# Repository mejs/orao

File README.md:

Orao: Yugoslav 8-bit school microcomputer
=====================================

Orao was an 8-bit computer developed by Miroslav Kocijan for PEL Varaždin in 1984. This repo includes roms, programs and tools for working with this computer. 

I've built a replica of this computer based on [Josip Perušanec's Orao 2007 project](http://www.deltasoft.com.hr/projects/orao2007.php?title=Orao%202007). This replica is fully compatible with the original, but it uses a single EPROM and RAM instead of multiple ones like the original.

### [Roms](https://github.com/mejs/orao/tree/master/roms)
There were 2 roms for the Orao:
* ROM 102: first rom version with basic (sic) BASIC and monitor program. This rom is in BCS.
* ROM 103: second rom version with advanced BASIC and monitor program. This rom is in English

Both of these roms were originally stored on two 2764 EPROMs, one would have the BASIC and the other the monitor. The version I have here combines both the 102 and 103 ROM versions with both BASIC and monitor into a single hex bin for loading onto a 27256 EPROM.

### [Orao rs232](https://github.com/mejs/orao/tree/master/orao_rs232)

The Orao has a built in RS232 TX meant for use with a printer, but no built in RX. In order to enable two way serial communication I built a 6551 based rs232 adapter. A gerbers file and a BOM are attached. I wrote a simple terminal emulator which consists of a BASIC and 6502 assembly. I'm still testing the interface.

### [Orao keyboard](https://github.com/mejs/orao/tree/master/orao_keyboard)

Since I don't own an original Orao, I needed a way to connect a regular PS2 keyboard to the replica. This is a work in progress project for an Arduino based interface that uses an MT8816 analog switch matrix to use a PS2 keyboard with the Orao. The interface supports all Orao keys and key combinations including PF keys, control and shift key support. You can find the list of all Orao key combinations [here (in BCS)](https://github.com/mejs/orao/tree/master/orao_keyboard/combinations.png) I've used an Arduino Nanofor testing.

Orao's keyboard input works by shorting connections between 6 data lines (D4-D7) and 10 address lines (A0-A9). When a key is pressed, the connection is shorted between corresponding lines to input a key press. I.e., to type "A", the key short address line A7 and data line D5. MT8816 is an analog switch relay. It contains a 8 x 16 array of crosspoint switches along with a 7 to 128 line decoder and latch circuits. The 8 lines are labeled Y0-Y7, and the 16 lines are labelled X0-X15. MT8816 can connect any Y line with any X line, and it can make multiple concurrent connections. Y1 to Y6 lines are connected to Orao's keyboard connector pins 1-6 (data lines D4-D7), and X0 to X9 are connected to Orao keyboard connector pins 7-16 (address lines A0-A9).

MT8816 connections are selected by seting bits on address inputs AX0-Ax3 and AY0-AY3. The addresses are defined in the [MT8816 datasheet](https://github.com/mejs/orao/tree/master/orao_keyboard/MT8816-datasheet.pdf) in Table 1 - Address Decode Truth Table on page 11. Address inputs are connected to Arduino digital I/O pins 8-14. Arduino uses PS2KeyAdvanced library to read keycodes from the connected PS/2 keyboard, connected to digital I/O pins 2 and 3. When a key is pressed (i.e. 32833 for A), Arduino sets the bits on the address inputs (1100101 for A), raises MT8816 data pin to save it to memory, raises and lowers strobe, holds for 22ms, then lowers data and raises reset. This makes the connection between A7 and D5 on the Orao.

Due to the physical difference between modern, Model-M compatible keyboards and Orao's keyboard, I've made the following key placement decisions:

* Insert key is used for * : Orao key
* Home key is used for / ? Orao key
* Backspace is used as left arrow key in addition to the actual left arrow key because it effectively works as backspace

This project was inspired by Marko Šolajić's [galaksija-keyboard-interface project](https://github.com/msolajic/galaksija-keyboard-interface) and the [C64-keyboard project](https://github.com/Hartland/C64-Keyboard)

I've designed and manufactured a board that can mount into the keyboard socket on the Orao 2007 clone. The Eagle files are available [here](https://github.com/mejs/orao/tree/master/orao_keyboard/eagle) and the gerber files are [here](https://github.com/mejs/orao/tree/master/orao_keyboard/gerbers).

### [Orao 2007 Gerbers](https://github.com/mejs/orao/tree/master/schematics)

The gerbers files hosted on Josip Perušanec's website include [one connection missing in the gerbers](https://twitter.com/mejs/status/1338876219308322817), preventing video output without an additional jumper. The version hosted here fixes this.

### [Manuals](https://github.com/mejs/orao/tree/master/manuals)

I've used a number of manuals while working on the Orao, especially the manual for the never released DIY kit that was [posted online by RetroInfo](https://retroinfo.hr/dvije-knjige-za-pel-orao/).

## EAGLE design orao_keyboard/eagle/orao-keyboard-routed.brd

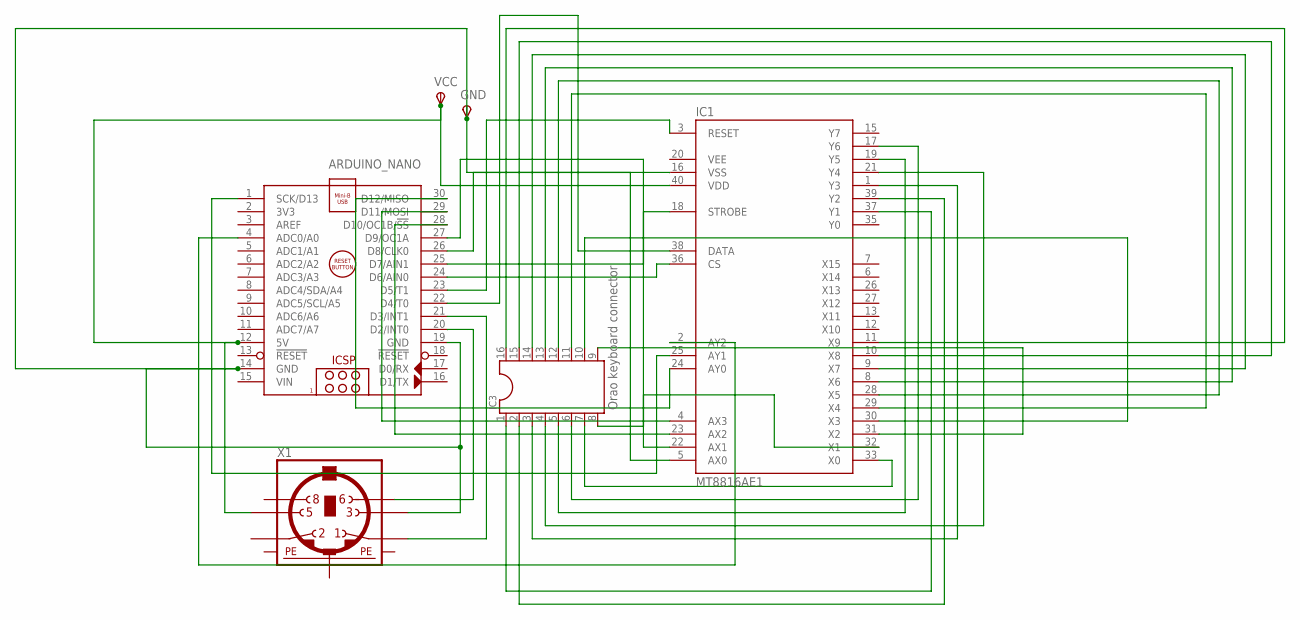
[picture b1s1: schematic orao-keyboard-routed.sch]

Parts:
ARDUINO_NANO: ARDUINO_NANO
GND: TPSPAD1-13; P1-13
IC1: MT8816AE1; DIL40
IC3: Orao keyboard connector; SOCKED-16
VCC: TPSPAD1-13; P1-13
X1: MINI_DIN_6; M_DIN6

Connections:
unnamed: ARDUINO_NANO.20 (D2/INT0), X1.6
unnamed: ARDUINO_NANO.21 (D3/INT1), X1.1
unnamed: IC1.37 (Y1), IC3.1
unnamed: IC1.39 (Y2), IC3.2
unnamed: IC1.1 (Y3), IC3.3
unnamed: IC1.21 (Y4), IC3.4
unnamed: IC1.19 (Y5), IC3.5
unnamed: IC1.17 (Y6), IC3.6
unnamed: IC1.33 (X0), IC3.7
unnamed: IC1.32 (X1), IC3.8
unnamed: IC1.31 (X2), IC3.9
unnamed: IC1.30 (X3), IC3.10
unnamed: IC1.29 (X4), IC3.11
unnamed: IC1.28 (X5), IC3.12
unnamed: IC1.8 (X6), IC3.13
unnamed: IC1.9 (X7), IC3.14
unnamed: IC1.10 (X8), IC3.15
unnamed: IC1.11 (X9), IC3.16
unnamed: ARDUINO_NANO.22 (D4/T0), IC1.38 (DATA)
unnamed: ARDUINO_NANO.23 (D5/T1), IC1.3 (RESET)
unnamed: ARDUINO_NANO.24 (D6/AIN0), IC1.36 (CS)
unnamed: ARDUINO_NANO.25 (D7/AIN1), IC1.18 (STROBE)
unnamed: ARDUINO_NANO.26 (D8/CLK0), IC1.5 (AX0)
unnamed: ARDUINO_NANO.27 (D9/OC1A), IC1.22 (AX1)
unnamed: ARDUINO_NANO.28 (D10/OC1B/!SS), IC1.23 (AX2)
unnamed: ARDUINO_NANO.29 (D11/MOSI), IC1.4 (AX3)
unnamed: ARDUINO_NANO.30 (D12/MISO), IC1.24 (AY0)
unnamed: ARDUINO_NANO.1 (SCK/D13), IC1.25 (AY1)
unnamed: ARDUINO_NANO.4 (ADC0/A0), IC1.2 (AY2)
unnamed: ARDUINO_NANO.12 (5V), IC1.40 (VDD), VCC.TP, X1.5
unnamed: ARDUINO_NANO.14 (GND), ARDUINO_NANO.19 (GND), GND.TP, IC1.16 (VSS), X1.3
PE1: X1.SH1 (PE1)
PE2: X1.SH2 (PE2)
PE3: X1.SH3 (PE3)
VEE: IC1.20 (VEE)
VIN: ARDUINO_NANO.15 (VIN)

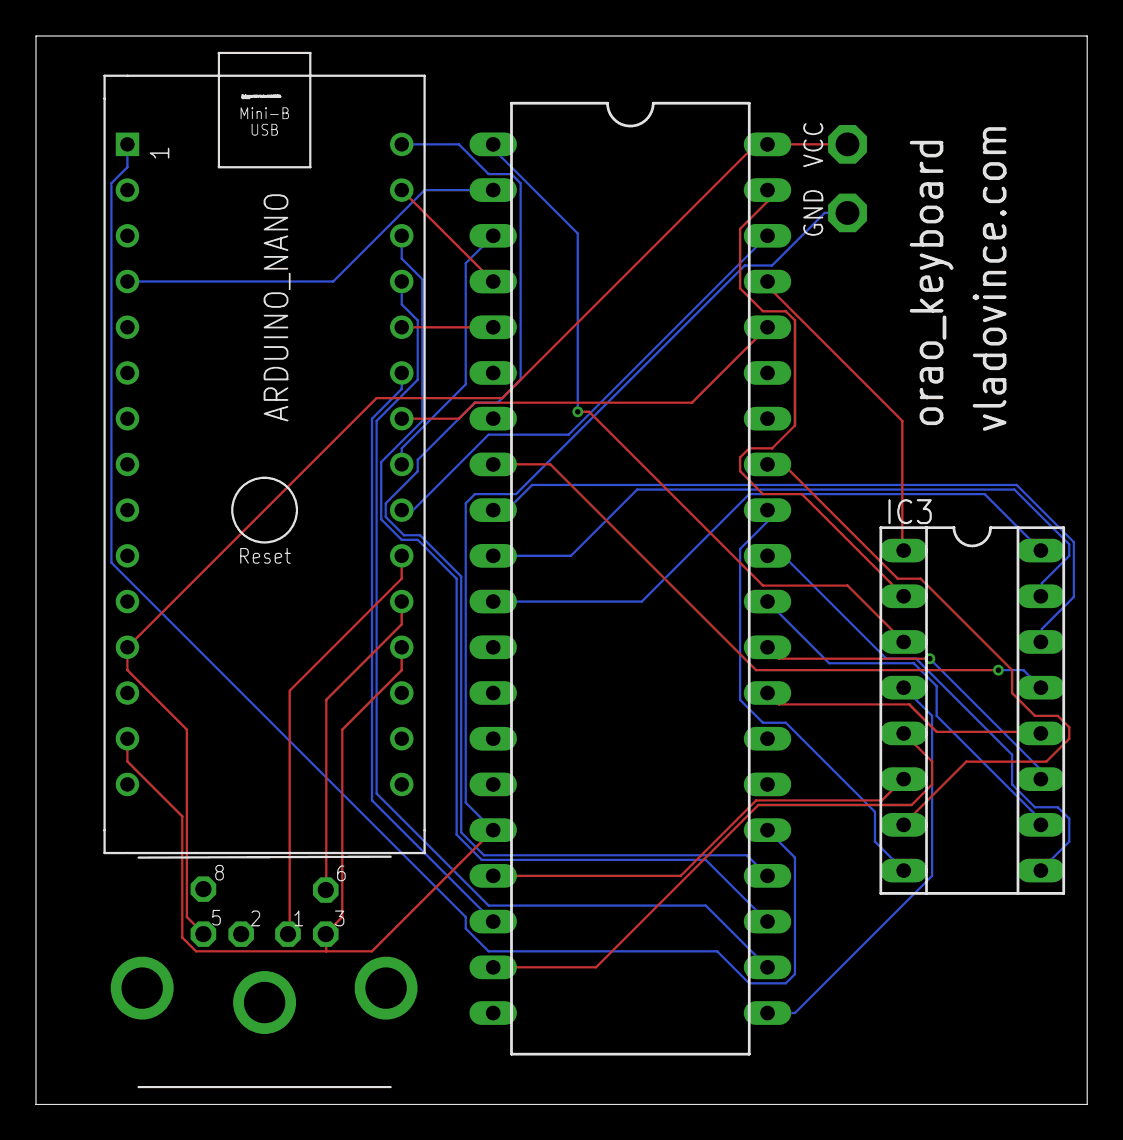
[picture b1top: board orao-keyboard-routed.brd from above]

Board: 2 copper layers, 58.4 x 59.4 mm, 6 parts (0 on the bottom side), 31 nets.

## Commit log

2020-12-18 added gerb
2020-12-18 added readme
2021-03-23 added keyboard files
2021-03-24 added images and roms
2021-03-24 added manuals
2021-03-24 added images
2021-03-24 added schematic
2021-03-25 added kbdcsh.png
2021-03-28 added extended delay to 100ms for keypress
2021-08-11 fixed dj and sh key mapping
2021-08-11 fixed repeating key presses
2021-09-28 new keyboard gerbs and arduino code updates
2022-01-22 specloader
2022-01-24 fixed PS/2 pinout
2022-05-01 added rom listing
2022-05-01 rom listing
2022-05-02 rom 102 listing
2022-05-24 rs232
2022-05-29 added rs232 gerbers and bom
2022-05-30 img updated
2022-10-24 orao terminal updated
2022-10-24 folders updated
2022-11-06 term emulator added backspace
2022-11-06 backspace ready
2022-11-13 imgs added
2022-11-13 README edited
2022-11-28 updated BOM and gerbers
2022-11-28 updated oraoterm wav
2022-11-28 updated instructions
2022-12-15 update .asm with + symbol
2022-12-15 implemented + sign in .wav terminal programs
2022-12-16 added ampersand to orao terminal emulator
2023-01-16 implemented shift in orao term
2023-01-16 implemented capital letters for orao terminal ver 0.30
2023-01-16 orao term v0.31
2023-01-19 implemented capital letters for orao terminal ver 0.32
2023-01-20 orao terminal ver 0.33 quick local responses fixed by implementing dtr every time keys are pressed
2023-01-20 orao terminal ver 0.34
2023-01-21 orao terminal ver 0.35
2023-01-22 orao terminal ver 0.36
2023-01-22 orao terminal ver 0.37
2023-01-23 orao terminal ver 0.38
2023-01-25 orao terminal ver 0.39
2023-05-09 added orao uvod u rad i programiranje books
2023-05-16 added orao rs232 schematic
2024-05-27 added orao expansion adapter from orao2007 to original orao
